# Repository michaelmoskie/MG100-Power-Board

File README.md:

# MG100-Power-Board
Replacement Power Board PCB for Marshall MG100 Solid State Amplifier

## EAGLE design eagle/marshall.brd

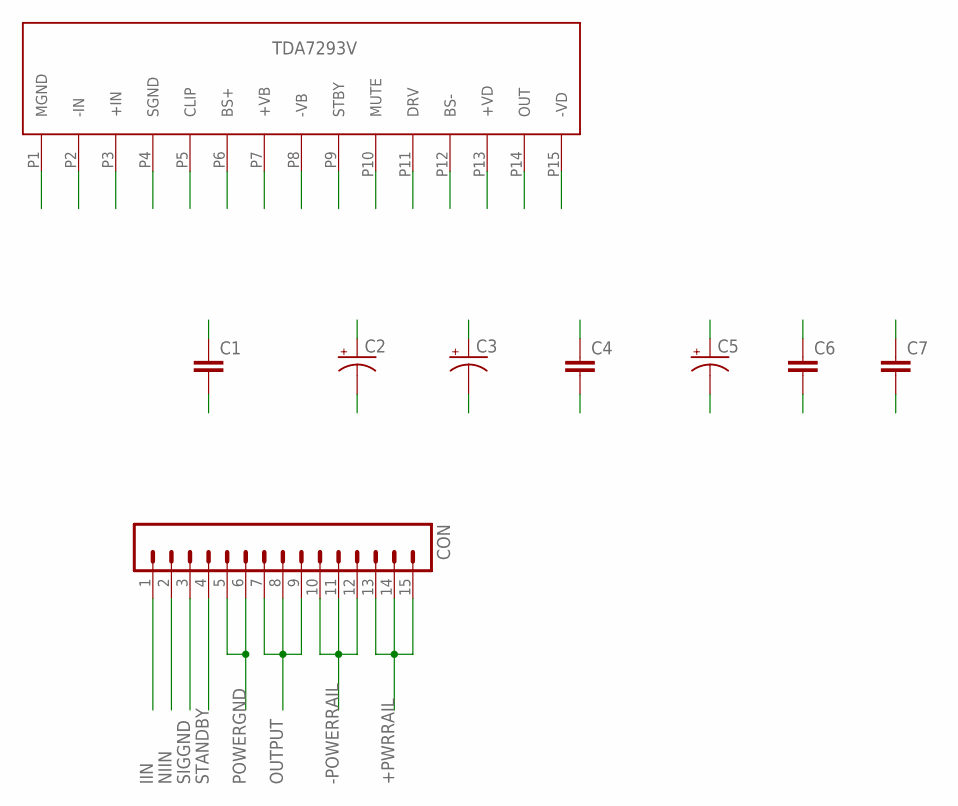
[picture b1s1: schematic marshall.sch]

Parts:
C1, C4, C6, C7: CAPPTH1; CAP-PTH-5MM
C2, C3, C5: CAP_POLPTH2; CPOL-RADIAL-10UF-25V
CON: M15; 1X15
U$1: TDA7293V

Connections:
+PWRRAIL: C1.1, C2.1 (+), CON.13, CON.14, CON.15, U$1.P7 (+VB), U$1.P10 (MUTE), U$1.P13 (+VD)
-POWERRAIL: C3.2 (-), C4.1, CON.10, CON.11, CON.12, U$1.P8 (-VB), U$1.P15 (-VD)
C5+: C5.1 (+), U$1.P12 (BS-)
C5-: C5.2 (-), U$1.P6 (BS+)
IIN: C6.2, C7.2, CON.1
NIIN: C6.1, CON.2, U$1.P3 (+IN)
OUTPUT: CON.7, CON.8, CON.9, U$1.P14 (OUT)
POWERGND: C1.2, C2.2 (-), C3.1 (+), C4.2, CON.5, CON.6, U$1.P1 (MGND)
SIGGND: C7.1, CON.3, U$1.P4 (SGND)
STANDBY: CON.4, U$1.P9 (STBY)

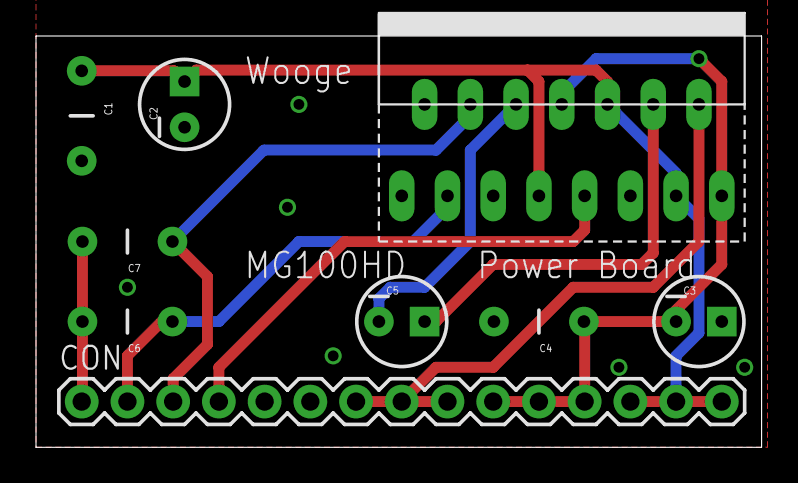
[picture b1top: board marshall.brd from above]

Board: 2 copper layers, 40.3 x 22.9 mm, 9 parts (0 on the bottom side), 10 nets.

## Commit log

2015-04-16 Added Board Images
2015-04-16 Eagle Files Added

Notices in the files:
parts and their libraries:
SparkFun-Connectors: Licensing: Creative Commons ShareAlike 4.0 International - https://creativecommons.org/licenses/by-sa/4.0
